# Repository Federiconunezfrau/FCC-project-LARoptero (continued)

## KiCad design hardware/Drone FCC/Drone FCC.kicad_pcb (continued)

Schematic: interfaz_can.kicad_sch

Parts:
C5, C6: 2.2u; C_0603_1608Metric_Pad1.08x0.95mm_HandSolder
C7, C8: 100nF; C_0402_1005Metric_Pad0.74x0.62mm_HandSolder
J15: CAN 1 Connector 1; HRS_DF13A-3P-1.25H(21)
J16: CAN 2 Connector 1; HRS_DF13A-3P-1.25H(21)
R1, R2, R6: 0; R_0402_1005Metric_Pad0.72x0.64mm_HandSolder
R3, R4: 10k; R_0402_1005Metric_Pad0.72x0.64mm_HandSolder
R5: 510; R_0402_1005Metric_Pad0.72x0.64mm_HandSolder
U1, U2: SN65HVD230; SOIC-8_3.9x4.9mm_P1.27mm

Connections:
3V3: C5.2, C6.2, C7.2, C8.2, U1.3 (VCC), U2.3 (VCC); also elsewhere on the board
/Interfaz_CAN/CAN1+: J15.2, U1.7 (CANH)
/Interfaz_CAN/CAN1-: J15.3, U1.6 (CANL)
/Interfaz_CAN/CAN1_RX: R1.1; also elsewhere on the board
/Interfaz_CAN/CAN1_TX: R5.1; also elsewhere on the board
/Interfaz_CAN/CAN2+: J16.2, U2.7 (CANH)
/Interfaz_CAN/CAN2-: J16.3, U2.6 (CANL)
/Interfaz_CAN/CAN2_RX: R2.1; also elsewhere on the board
/Interfaz_CAN/CAN2_TX: R6.1; also elsewhere on the board
GND: C5.1, C6.1, C7.1, C8.1, J15.1, J16.1, R3.2, R4.2, U1.2 (GND), U2.2 (GND); also elsewhere on the board
unnamed: R1.2, U1.4 (R)
unnamed: R2.2, U2.4 (R)
unnamed: R3.1, U1.8 (Rs)
unnamed: R4.1, U2.8 (Rs)
unnamed: R5.2, U1.1 (D)
unnamed: R6.2, U2.1 (D)

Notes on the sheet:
Capacitor de desacople, cerámico
Resistores para limitar la corriente en los pines. En caso de ringing, sirve para compensar. Puede ponerse otro valor, o un resistor de 0 Ohms

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
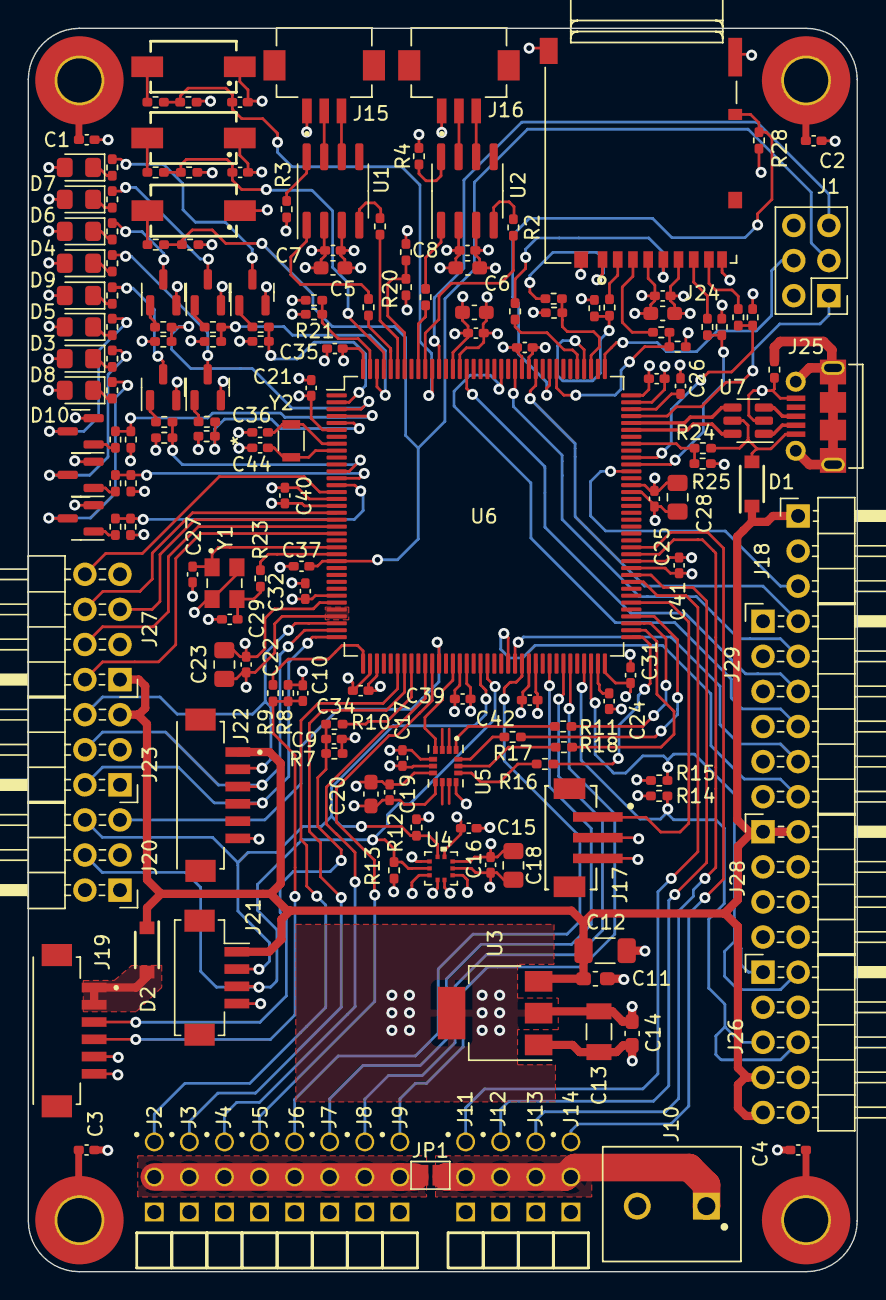
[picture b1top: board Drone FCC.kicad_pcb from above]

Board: 4 copper layers, 60.0 x 90.0 mm, 180 parts (0 on the bottom side), 140 nets.

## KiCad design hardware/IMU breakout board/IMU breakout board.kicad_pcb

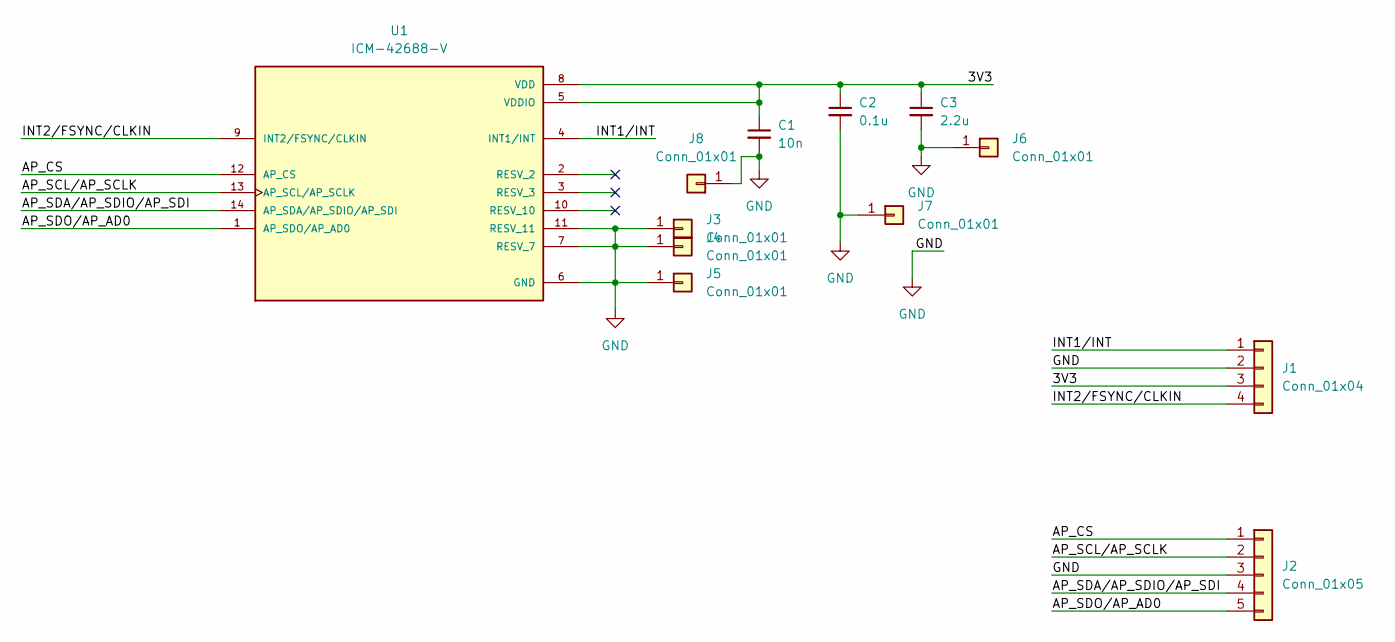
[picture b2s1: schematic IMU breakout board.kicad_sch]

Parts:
C1: 10n; C_0603_1608Metric_Pad1.08x0.95mm_HandSolder
C2: 0.1u; C_0603_1608Metric_Pad1.08x0.95mm_HandSolder
C3: 2.2u; C_0603_1608Metric_Pad1.08x0.95mm_HandSolder
J1: Conn_01x04; PinHeader_1x04_P2.54mm_Vertical
J2: Conn_01x05; PinHeader_1x05_P2.54mm_Vertical
J3, J4, J5, J6, J7, J8: Conn_01x01; Pin_D0.7mm_L6.5mm_W1.8mm_FlatFork
U1: ICM-42688-V; PQFN50P300X250X97-14N

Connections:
/3V3: C1.1, C2.1, C3.1, J1.3, U1.5 (VDDIO), U1.8 (VDD)
/AP_CS: J2.1, U1.12 (AP_CS)
/AP_SCL/AP_SCLK: J2.2, U1.13 (AP_SCL/AP_SCLK)
/AP_SDA/AP_SDIO/AP_SDI: J2.4, U1.14 (AP_SDA/AP_SDIO/AP_SDI)
/AP_SDO/AP_AD0: J2.5, U1.1 (AP_SDO/AP_AD0)
/INT1/INT: J1.1, U1.4 (INT1/INT)
/INT2/FSYNC/CLKIN: J1.4, U1.9 (INT2/FSYNC/CLKIN)
GND: C1.2, C2.2, C3.2, J1.2, J2.3, J3.1, J4.1, J5.1, J6.1, J7.1, J8.1, U1.6 (GND), U1.7 (RESV_7), U1.11 (RESV_11)

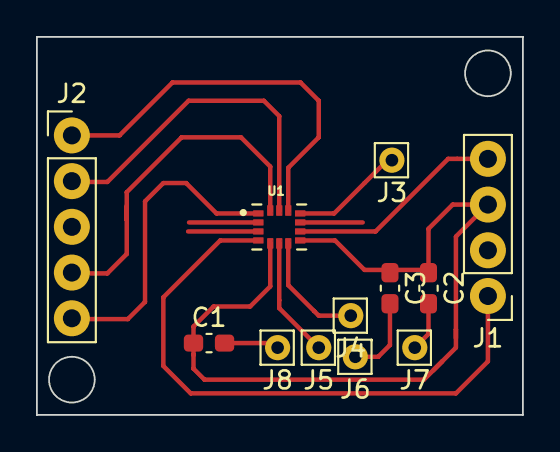
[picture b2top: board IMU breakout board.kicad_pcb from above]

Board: 2 copper layers, 27.0 x 21.0 mm, 12 parts (0 on the bottom side), 8 nets.

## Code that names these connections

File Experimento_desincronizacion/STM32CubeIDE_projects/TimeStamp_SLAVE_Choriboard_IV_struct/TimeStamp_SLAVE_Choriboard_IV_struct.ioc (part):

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Mcu.Name=STM32F746ZGTx
Mcu.Package=LQFP144
Mcu.UserName=STM32F746ZGTx
PA11.Mode=Device_Only
PA11.Signal=USB_OTG_FS_DM
PA12.Mode=Device_Only
PA12.Signal=USB_OTG_FS_DP
PA13.Mode=Serial_Wire
PA13.Signal=SYS_JTMS-SWDIO
PA14.Mode=Serial_Wire
PA14.Signal=SYS_JTCK-SWCLK
PB12.GPIOParameters=PinState,GPIO_Label
PB12.GPIO_Label=IMU_CS
PB12.PinState=GPIO_PIN_SET
PB12.Signal=GPIO_Output
PB13.Mode=Full_Duplex_Master
PB13.Signal=SPI2_SCK
PB14.Mode=Full_Duplex_Master
PB14.Signal=SPI2_MISO
PB15.Mode=Full_Duplex_Master
PB15.Signal=SPI2_MOSI
PB5.Mode=CAN_Activate
PB5.Signal=CAN2_RX
PB6.Mode=CAN_Activate
PB6.Signal=CAN2_TX
PB8.Mode=CAN_Activate
PB8.Signal=CAN1_RX
PB9.Mode=CAN_Activate
PB9.Signal=CAN1_TX
PD3.GPIOParameters=GPIO_Label
PD3.GPIO_Label=uSD_SW
PD3.Signal=GPIO_Input
PE1.GPIOParameters=GPIO_Label
PE1.GPIO_Label=LED3
PE1.Signal=GPIO_Output
PE3.GPIOParameters=GPIO_Label
PE3.GPIO_Label=LED2
PE3.Signal=GPIO_Output
PE4.GPIOParameters=GPIO_Label
PE4.GPIO_Label=LED1
PE4.Signal=GPIO_Output
PE5.GPIOParameters=GPIO_Label
PE5.GPIO_Label=LED7
PE5.Signal=GPIO_Output
PE6.GPIOParameters=GPIO_Label
PE6.GPIO_Label=LED4
PE6.Signal=GPIO_Output
PF14.Mode=I2C
PF14.Signal=I2C4_SCL
PF15.Mode=I2C
PF15.Signal=I2C4_SDA
PF2.GPIOParameters=GPIO_Label
PF2.GPIO_Label=LED6
PF2.Signal=GPIO_Output
PF3.GPIOParameters=GPIO_Label
PF3.GPIO_Label=LED8
PF3.Signal=GPIO_Output
PF4.GPIOParameters=GPIO_Label
PF4.GPIO_Label=LED5
PF4.Signal=GPIO_Output
PH0/OSC_IN.Mode=HSE-External-Oscillator
PH0/OSC_IN.Signal=RCC_OSC_IN
PH1/OSC_OUT.Mode=HSE-External-Oscillator
PH1/OSC_OUT.Signal=RCC_OSC_OUT
RCC.HSE_VALUE=12000000
RCC.SYSCLKFreq_VALUE=216000000
RCC.SYSCLKSource=RCC_SYSCLKSOURCE_PLLCLK
board=custom

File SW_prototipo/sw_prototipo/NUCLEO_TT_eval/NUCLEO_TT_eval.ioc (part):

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Mcu.Name=STM32F746ZGTx
Mcu.Package=LQFP144
Mcu.UserName=STM32F746ZGTx
PA1.GPIOParameters=GPIO_Label
PA1.GPIO_Label=RMII_REF_CLK [LAN8742A-CZ-TR_REFCLK0]
PA1.Signal=ETH_REF_CLK
PA10.GPIOParameters=GPIO_Label
PA10.GPIO_Label=USB_ID
PA10.Signal=USB_OTG_FS_ID
PA11.GPIOParameters=GPIO_Label
PA11.GPIO_Label=USB_DM
PA11.Signal=USB_OTG_FS_DM
PA12.GPIOParameters=GPIO_Label
PA12.GPIO_Label=USB_DP
PA12.Signal=USB_OTG_FS_DP
PA13.GPIOParameters=GPIO_Label
PA13.GPIO_Label=TMS
PA13.Mode=Serial_Wire
PA13.Signal=SYS_JTMS-SWDIO
PA14.GPIOParameters=GPIO_Label
PA14.GPIO_Label=TCK
PA14.Mode=Serial_Wire
PA14.Signal=SYS_JTCK-SWCLK
PA2.GPIOParameters=GPIO_Label
PA2.GPIO_Label=RMII_MDIO [LAN8742A-CZ-TR_MDIO]
PA2.Signal=ETH_MDIO
PA7.GPIOParameters=GPIO_Label
PA7.GPIO_Label=RMII_CRS_DV [LAN8742A-CZ-TR_CRS_DV]
PA7.Signal=ETH_CRS_DV
PA8.GPIOParameters=GPIO_Label
PA8.GPIO_Label=USB_SOF [TP1]
PA8.Signal=USB_OTG_FS_SOF
PA9.GPIOParameters=GPIO_Label
PA9.GPIO_Label=USB_VBUS
PA9.Signal=USB_OTG_FS_VBUS
PB0.GPIOParameters=GPIO_Label
PB0.GPIO_Label=LD1 [Green]
PB0.Signal=GPIO_Output
PB10.GPIOParameters=GPIO_Label
PB10.GPIO_Label=IMU_SCK
PB10.Mode=Full_Duplex_Master
PB10.Signal=SPI2_SCK
PB13.GPIOParameters=GPIO_Label
PB13.GPIO_Label=RMII_TXD1 [LAN8742A-CZ-TR_TXD1]
PB13.Signal=ETH_TXD1
PB14.GPIOParameters=GPIO_Label
PB14.GPIO_Label=LD3 [Red]
PB14.Signal=GPIO_Output
PB3.GPIOParameters=GPIO_Label
PB3.GPIO_Label=SW0
PB3.Signal=SYS_JTDO-SWO
PB7.GPIOParameters=GPIO_Label
PB7.GPIO_Label=LD2 [Blue]
PB7.Signal=GPIO_Output
PC1.GPIOParameters=GPIO_Label
PC1.GPIO_Label=RMII_MDC [LAN8742A-CZ-TR_MDC]
PC1.Signal=ETH_MDC
PC13.GPIOParameters=GPIO_Label
PC13.GPIO_Label=USER_Btn [B1]
PC13.Signal=GPXTI13
PC14/OSC32_IN.Mode=LSE-External-Oscillator
PC14/OSC32_IN.Signal=RCC_OSC32_IN
PC15/OSC32_OUT.Mode=LSE-External-Oscillator
PC15/OSC32_OUT.Signal=RCC_OSC32_OUT
PC2.GPIOParameters=GPIO_Label
PC2.GPIO_Label=IMU_MISO
PC2.Mode=Full_Duplex_Master
PC2.Signal=SPI2_MISO
PC3.GPIOParameters=GPIO_Label
PC3.GPIO_Label=IMU_MOSI
PC3.Mode=Full_Duplex_Master
PC3.Signal=SPI2_MOSI
PC4.GPIOParameters=GPIO_Label
PC4.GPIO_Label=RMII_RXD0 [LAN8742A-CZ-TR_RXD0]
PC4.Signal=ETH_RXD0
PC5.GPIOParameters=GPIO_Label
PC5.GPIO_Label=RMII_RXD1 [LAN8742A-CZ-TR_RXD1]
PC5.Signal=ETH_RXD1
PD0.Mode=CAN_Activate
PD0.Signal=CAN1_RX
PD1.Mode=CAN_Activate
PD1.Signal=CAN1_TX
PD8.GPIOParameters=GPIO_PuPd,GPIO_Label
PD8.GPIO_Label=STLK_RX [STM32F103CBT6_PA3]
PD8.GPIO_PuPd=GPIO_PULLUP
PD8.Mode=Asynchronous
PD8.Signal=USART3_TX
PD9.GPIOParameters=GPIO_PuPd,GPIO_Label
PD9.GPIO_Label=STLK_TX [STM32F103CBT6_PA2]
PD9.GPIO_PuPd=GPIO_PULLUP
PD9.Mode=Asynchronous
PD9.Signal=USART3_RX
PE10.GPIOParameters=GPIO_Label
PE10.GPIO_Label=IMU_CS
PE10.Signal=GPIO_Output
PG11.GPIOParameters=GPIO_Label
PG11.GPIO_Label=RMII_TX_EN [LAN8742A-CZ-TR_TXEN]
PG11.Signal=ETH_TX_EN
PG13.GPIOParameters=GPIO_Label
PG13.GPIO_Label=RMII_TXD0 [LAN8742A-CZ-TR_TXD0]
PG13.Signal=ETH_TXD0
PG6.GPIOParameters=GPIO_Label
PG6.GPIO_Label=USB_PowerSwitchOn [STMPS2151STR_EN]
PG6.Signal=GPIO_Output
PG7.GPIOParameters=GPIO_Label
PG7.GPIO_Label=USB_OverCurrent [STMPS2151STR_FAULT]
PG7.Signal=GPIO_Input
PH0/OSC_IN.GPIOParameters=GPIO_Label
PH0/OSC_IN.GPIO_Label=MCO [STM32F103CBT6_PA8]
PH0/OSC_IN.Mode=HSE-External-Clock-Source
PH0/OSC_IN.Signal=RCC_OSC_IN
PH1/OSC_OUT.Mode=HSE-External-Clock-Source
PH1/OSC_OUT.Signal=RCC_OSC_OUT
RCC.HSE_VALUE=8000000
RCC.SYSCLKFreq_VALUE=72000000
RCC.SYSCLKSource=RCC_SYSCLKSOURCE_PLLCLK
RCC.SYSCLKSourceVirtual=RCC_SYSCLKSOURCE_PLLCLK
board=NUCLEO-F746ZG
boardIOC=true

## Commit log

2022-11-20 esquematico barometro I2C
2022-11-21 changed ICM-42688-P for ICM-42688-V
2022-12-05 add connectors for PWM
2022-12-06 started schematic
2022-12-07 all sensors on same schematic subpage
2022-12-20 add USB connector
2022-12-30 DSM: deleted dupont conn, PPM: deleted DF-13 conn
2023-01-05 finished IMU basic schematic
2023-01-08 add IMU breakout board PCB
2023-01-08 finish barometer schematic
2023-01-08 moved MCU to hierarchical sheet
2023-01-11 IMU board: added holes to pcb
2023-01-12 changed mag connector for GPS module DF-13
2023-01-14 add LDO 3V3 to schematic
2023-01-15 add functional schematic for microSD
2023-01-16 changed usb 2.0 AB connector for usb 2.0 B
2023-01-27 add usb TVS diodes and mcu pin assignment
2023-02-06 fix connection of TVS USB diode IC
2023-02-09 finish SWD functional schematic
2023-02-14 add soft-start for USB connector
2023-02-26 add HSE and LSE crystals to schematic
2023-03-05 add CAN schematic
2023-03-11 rearranged FCC schematic
2023-03-16 add external communication connectors
2023-03-18 re enumeration of components
2023-04-02 start routing
2023-04-08 continued preliminar routing
2023-04-13 continue routing
2023-04-23 routing: connected everything
2023-04-25 positioning of componentes 80x80 pcb
2023-05-02 positioned components in 100x60 board with incomplete routing
2023-05-02 todo: route SWD connector
2023-05-03 included SWD header in routing
2023-05-07 added LEDs in routing
2023-05-07 included all components on PCB
2023-05-07 add 3D models to footprints
2023-05-14 LDO layout on PCB
2023-05-20 CAN PCB layout, positioned series resistors CAN TX and CAN RX
2023-05-20 fix: moved series resistors from CANTX2 and CANRX2
2023-05-26 routing of HSE crystal oscillator
2023-05-26 finished
2023-05-28 finish SD routing
2023-05-28 add series resistor SPI buses
2023-05-29 add TVS diodes for SPI and ESD capacitors
2023-05-31 add TVS diodes for all the dupont pins
2023-06-01 continued routing missing connections
2023-06-04 added missing TVS diodes
2023-06-04 set values of resistors for LEDs
2023-06-04 moved some LEDs over the oppsoite layer of microSD footprint
2023-06-05 rounded corners
2023-06-07 minor changes
2023-06-10 moved microSD to top layer. Also transistors for LEDs
2023-06-10 routed transistors and LEDs on top layer
2023-06-11 length matching microSD
2023-06-24 add latex files of thesis doc
2023-06-28 changes on latex
2023-06-29 added images for section 3.4.2
2023-07-16 Added 4 way redundancy explanation, section 3.5
2023-07-23 started with Time-Triggered Architecture explanation
2023-08-06 finish simple explanation of Time Triggered Architecture
2023-08-12 minor spelling errors corrected
2023-08-13 updated dimensions for new stackup
2023-08-13 re routed CAN and USB with new dimensions
2023-08-13 changed sw with smaller sw
2023-08-13 removed all the TVS from the PCB and SCH
2023-08-13 re routed new smaller SW
2023-08-13 re positioned resistors and capacitors for reducing space
2023-08-14 re routed everything with newer dimensions
2023-08-14 tidying up the schematic
2023-08-14 re enumeation of componentes
2023-08-19 moved external SPI tracks to TOP layer. Moved external I2C pull ups to TOP layer
2023-08-22 updated PCB.pdf file
2023-09-02 update of thesis plan document
2023-09-03 first version of thesis plan document
2023-09-04 fixed KiCad DRC errors
2023-09-04 length matching SD
2023-09-05 update PCB and schematic
2023-09-05 modifications on thesis plan doc
2023-09-06 connected CAN transcievers slope control pin resistor to gnd
2023-09-06 minor modifications
2023-09-08 fixed 3d model USB connector position
2023-09-08 updated gantt
2023-09-09 space between barometer and spectrum conn
2023-09-17 moved NRST cap near mcu pin, changed v meas adc pin
2023-09-17 fix error on clearance track
2023-09-17 add PWR_FLAGs to schematic
2023-09-17 update schematic and PCB PDF files
2023-09-18 add resistor for optional connection of USB shield to GND plane
2023-09-18 fix minor warnings in kicad PCB
2023-09-22 fix USB shield connector to GND plane
2023-09-23 thesis plan final version
2023-10-01 minor changes PCB
2023-10-01 add ICM42688 very simple driver
2023-10-10 Add BOM file
2023-10-22 updated BOM with passive components
2023-10-22 add BOM in PDF
2023-10-22 fix BOM PDF
2023-11-10 started pcb documentation
2023-11-10 finish CAN PCB documentation
2023-11-13 finish LDO schematic section
2023-11-16 add avionics redundant system state of the art section
2023-11-16 add examples of commercial and COTS redundant FCCs
2023-11-18 add similar project examples
2023-11-18 add section for general requirements of redundancy
2023-11-19 add subsections for general requirements of redundancy
2023-11-21 add justification of CAN bus selection
2024-01-25 add content of microcontroller selection
2024-01-27 add python notebook, raw data and doc
2024-01-27 add STM32CubeIDE projects
2024-02-16 add STMCubeMX project
2024-02-24 add working projects for choriboard and nucleo
2024-02-25 add periodic sync task
2024-03-03 changed period send IMU data to 100 ms
2024-03-06 add task complementary filter pitch and roll
2024-03-09 add attitude comparison task
2024-04-01 Sections Objectivo and Introduccion
2024-04-02 started with section Diseño y Construccion de la Comptuadora de Vuelo
2024-04-06 Add structure of section Implementacion del Sistema Tolerante a Fallas
2024-04-06 fix IMU and barometer section, added magnetometer section
2024-04-08 completed subsubsection Interfaz de comunicacion CAN
2024-04-09 completed subsubsection Circuito de Alimentacion and Micro SD
2024-04-11 completed subsubsection USB, GPS and otras funcionalidades
2024-04-12 completed subsubsections PWM and SWD
2024-04-14 completed subsubsection Conectores para Control por Radio
2024-04-14 completed subsubsection Uso de Componentes de Grado Automotriz
2024-04-14 reduced size of subsubsection sensor IMU
2024-04-14 completed subsubsections Requerimientos Manufacturabilidad and IMU
2024-04-15 completed subsubsection Características del PCB
2024-04-16 completed subsubsection Comunicacion MicroSD
2024-04-16 Completed subsubsection Comunicacion USB
2024-04-16 add magnetometer image with axis
2024-04-17 completed subsubsection Layout del Regulador Lineal
2024-04-18 completed subsection Diagrama en Bloques y PCB Final
2024-04-25 corrections in subsection Descripcion de la Arquitectura Propuesta
2024-04-27 minor spellings in Descripcion de la Arquitectura Propuesta
2024-04-27 finished text subsubsection Scheduler
2024-04-27 finished text subsubsection Comunicacion a Traves del Bus
2024-04-27 minor spellings in Comunicacion a Traves del Bus
2024-04-27 finished text subsubsection Sincronizacion
2024-04-29 add text subsubsection Tareas de Ejemplo Adquisicion de Datos del Sensor IMU
2024-04-30 add text subsection Pruebas Realizadas
2024-04-30 add pictures for pruebas realizadas
2024-05-02 add pictures in Descripcion de la Arquitectura Propuesta
2024-05-02 add class diagram in subsubsection scheduler
2024-05-04 add scheduler and dispatcher pictures
2024-05-04 fix complementary filter math
2024-05-04 remove send IMU data task, moved get imu data and estimator on tick 0
2024-05-06 update with 10ms schedule
2024-05-11 finish section Implementacion del Sistema Tolerante a Fallas
2024-05-12 finish subsubsection Necesidad del Sincronismo entre Replicas
2024-05-12 finish subsubsection Necesidad del Consenso entre Replicas
2024-05-13 finish subsection Simplificacion del Problema
2024-05-17 changes in subsection Redundancias en Sistemas de Control de Vuelo en Aviones
2024-05-18 corrections in subsection Redundancias en Sistemas de Control de Vuelo en UAVs
2024-05-18 finish section Estado del Arte
2024-05-24 updated cover, fixed images, add schematic and PCB to appendix
2024-05-25 add description of previous versions of choriboard
2024-05-25 changed 5.1 to Antecedentes en el desarrollo de la Computadora de Vuelo
2024-05-26 finish section Conclusiones
2024-06-01 add oscilloscope can bus captures
2024-06-01 minor spelling corrections
2024-06-04 fixed bug watchdog reset
2024-06-18 started presentation
2024-06-20 add Introduccion and Sistemas Tolerantes a Fallas to presentation
2024-06-21 started Diseno y Construccion de la Computadora de Vuelo presentation
2024-07-03 add presentation pictures
2024-07-06 corrections of 8/6/2024
2024-07-06 corrected spelling errors
2024-09-22 add final presentation
2024-09-22 updated schematic and PCB pdf files
